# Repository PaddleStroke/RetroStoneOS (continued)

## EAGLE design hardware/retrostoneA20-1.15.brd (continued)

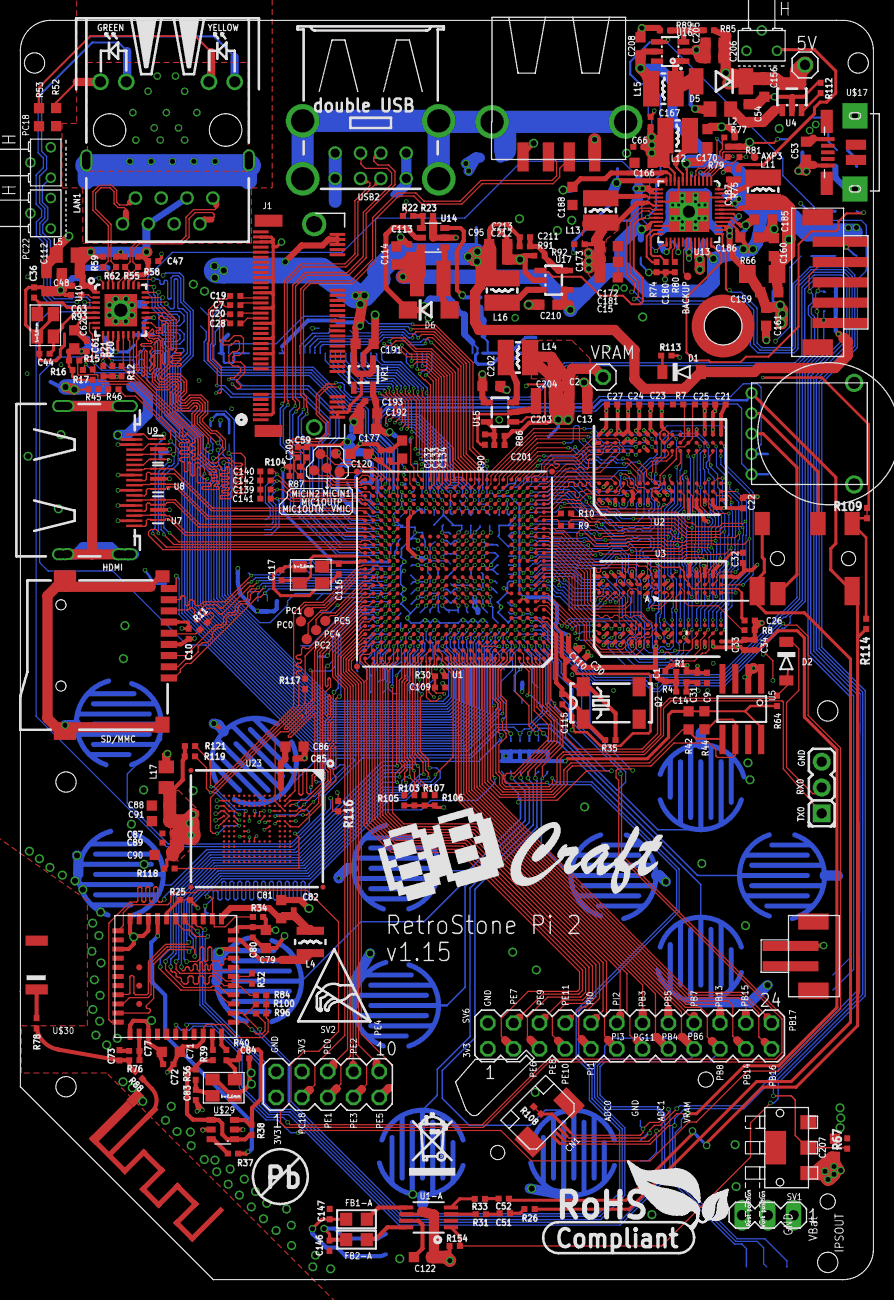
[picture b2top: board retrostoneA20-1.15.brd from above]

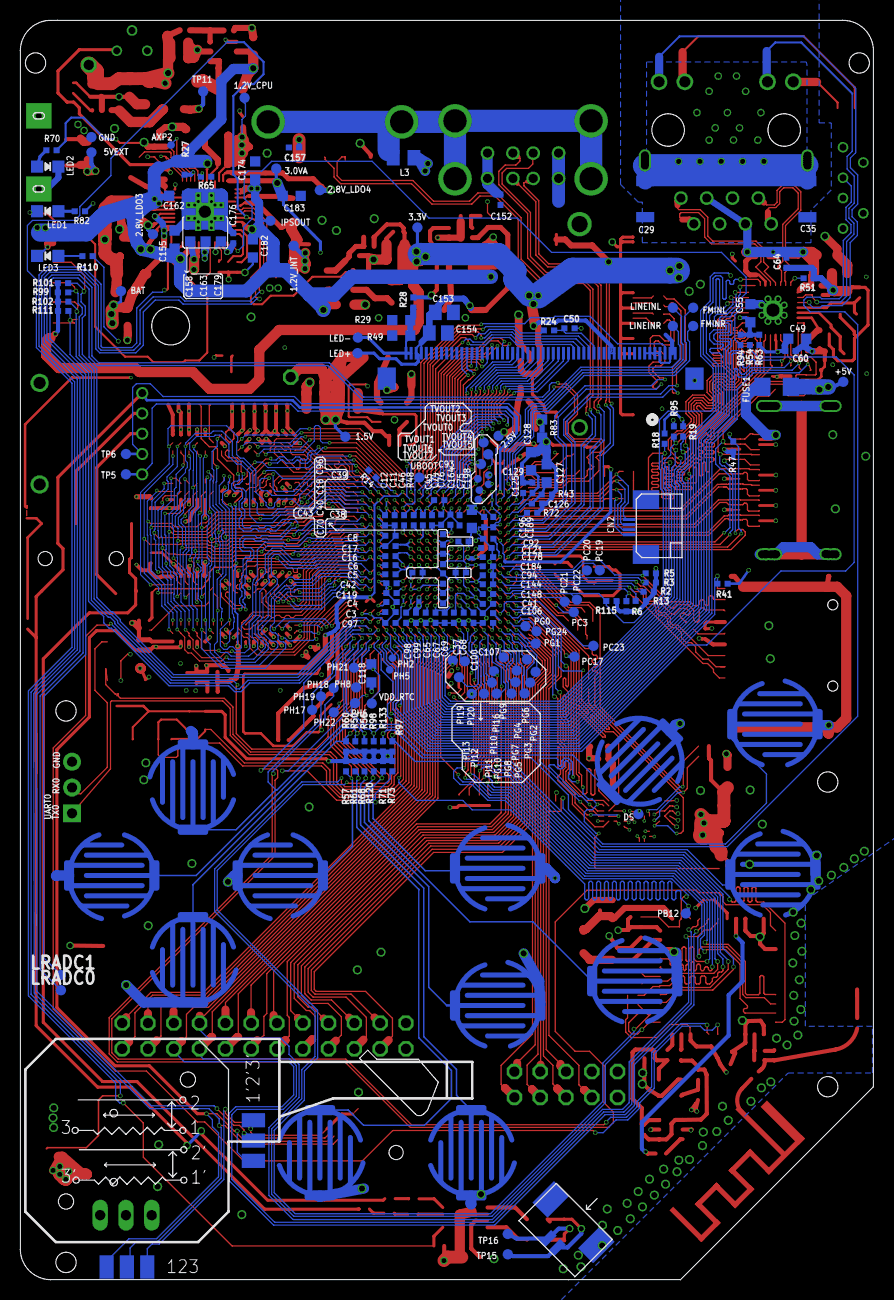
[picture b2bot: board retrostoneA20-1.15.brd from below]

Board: 4 copper layers, 84.0 x 124.0 mm, 477 parts (213 on the bottom side), 416 nets.

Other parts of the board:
U$9: PB
U$10: ESD_SYMBOL
U$11: RECYCLE_BIN1/8
U$12: ROHS
U$14: 8BCRAFTLOGO

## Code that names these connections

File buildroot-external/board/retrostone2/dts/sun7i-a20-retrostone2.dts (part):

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	/*
	 * Optional analog stick U$33 (FPC CN1, "Pro" part), read through the
	 * AXP209 ADC. The pots are fed from the 1.5 V net, the wipers go to AXP
	 * GPIO0 (X) and GPIO1 (Y). axp20x_adc raw unit is 0.5 mV, so full scale
	 * is ~3000. io-channels indexes are positions in axp20x_adc_channels[]:
	 * 5 = gpio0_v, 6 = gpio1_v (the old kernel exposed them as in_voltage3/4).
	 * X is inverted, like the production script (ABS_X = VREF - raw).
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	};

	/*
	 * PB2/PWM0 -> R22 -> CE of U14 (KA2707 LED boost), R23 pulls CE low.
	 * The boost runs from IPSOUT: there is no backlight enable GPIO and no
	 * backlight supply to switch (schematic v1.15).
	 */
	backlight: backlight {
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
	/*
	 * Face buttons, D-pad, START/SELECT. All switch to GND with an external
	 * 10k pull-up (active low). Every pin here is PH0-PH21, which have an
	 * external interrupt (EINTn) on the A20, so they are interrupt driven.
	 *
	 * Codes follow Documentation/input/gamepad.rst, which is positional:
	 * the Nintendo-style labels A (right) and B (bottom) map to BTN_EAST and
	 * BTN_SOUTH. This matches the production RetroArch autoconfig
	 * (PH0 = RetroPad A, PH11 = RetroPad B, PH12 = X, PH20 = Y).
	 * TODO(hw): confirm the physical A/B/X/Y positions on the case.
	 */
	gpio-keys {
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		button-a {
			label = "A";
			linux,code = <BTN_EAST>;
			gpios = <&pio 7 0 GPIO_ACTIVE_LOW>;	/* PH0, K2 */
		};

		button-b {
			label = "B";
			linux,code = <BTN_SOUTH>;
			gpios = <&pio 7 11 GPIO_ACTIVE_LOW>;	/* PH11, K4 */
		};

		button-x {
			label = "X";
			linux,code = <BTN_NORTH>;
			gpios = <&pio 7 12 GPIO_ACTIVE_LOW>;	/* PH12, K1 */
		};

		button-y {
			label = "Y";
			linux,code = <BTN_WEST>;
			gpios = <&pio 7 20 GPIO_ACTIVE_LOW>;	/* PH20, K3 */
		};

		/* Optional buttons (pads SELECT3/SELECT4 on the PCB) */
		button-c {
			label = "C";
			linux,code = <BTN_C>;
			gpios = <&pio 7 3 GPIO_ACTIVE_LOW>;	/* PH3, K5 */
		};

		button-z {
			label = "Z";
			linux,code = <BTN_Z>;
			gpios = <&pio 7 13 GPIO_ACTIVE_LOW>;	/* PH13, K6 */
		};

		button-start {
			label = "Start";
			linux,code = <BTN_START>;
			gpios = <&pio 7 14 GPIO_ACTIVE_LOW>;	/* PH14 */
		};

		button-select {
			label = "Select";
			linux,code = <BTN_SELECT>;
			gpios = <&pio 7 15 GPIO_ACTIVE_LOW>;	/* PH15 */
		};

		button-dpad-up {
			label = "D-pad Up";
			linux,code = <BTN_DPAD_UP>;
			gpios = <&pio 7 19 GPIO_ACTIVE_LOW>;	/* PH19 */
		};

		button-dpad-down {
			label = "D-pad Down";
			linux,code = <BTN_DPAD_DOWN>;
			gpios = <&pio 7 7 GPIO_ACTIVE_LOW>;	/* PH7 */
		};

		button-dpad-left {
			label = "D-pad Left";
			linux,code = <BTN_DPAD_LEFT>;
			gpios = <&pio 7 4 GPIO_ACTIVE_LOW>;	/* PH4 */
		};

		button-dpad-right {
			label = "D-pad Right";
			linux,code = <BTN_DPAD_RIGHT>;
			gpios = <&pio 7 16 GPIO_ACTIVE_LOW>;	/* PH16 */
		};
	};

	/*
	 * Shoulder buttons on the 5-pin JST connector U$4. PH22-PH27 have no
	 * EINT on the A20, so they are polled. Active low, external 10k pull-ups.
	 */
	gpio-keys-shoulder {
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		button-l1 {
			label = "L1";
			linux,code = <BTN_TL>;
			gpios = <&pio 7 23 GPIO_ACTIVE_LOW>;	/* PH23 */
		};

		button-r1 {
			label = "R1";
			linux,code = <BTN_TR>;
			gpios = <&pio 7 22 GPIO_ACTIVE_LOW>;	/* PH22 */
		};

		button-l2 {
			label = "L2";
			linux,code = <BTN_TL2>;
			gpios = <&pio 7 27 GPIO_ACTIVE_LOW>;	/* PH27 */
		};

		button-r2 {
			label = "R2";
			linux,code = <BTN_TR2>;
			gpios = <&pio 7 26 GPIO_ACTIVE_LOW>;	/* PH26 */
		};
	};

	/*
	 * Tact switches U$32 (PC18) and U$31 (PC22), active low with external
	 * 10k pull-ups. Port C has no EINT, so they are polled. The production
	 * firmware used them as brightness +/-; volume is an analog wheel, so
	 * brightness codes are the right default. Kept in their own input
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		key-brightness-up {
			label = "Brightness Up";
			linux,code = <KEY_BRIGHTNESSUP>;
			gpios = <&pio 2 18 GPIO_ACTIVE_LOW>;	/* PC18, U$32 */
		};

		key-brightness-down {
			label = "Brightness Down";
			linux,code = <KEY_BRIGHTNESSDOWN>;
			gpios = <&pio 2 22 GPIO_ACTIVE_LOW>;	/* PC22, U$31 */
		};
	};

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	leds {
		compatible = "gpio-leds";

		/* PH2 -> R110 (10k) -> LED3 (blue) -> GND: active high */
		led-0 {
			function = LED_FUNCTION_STATUS;
			color = <LED_COLOR_ID_BLUE>;
			gpios = <&pio 7 2 GPIO_ACTIVE_HIGH>;	/* PH2 */
			default-state = "off";
		};
	};
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	/* eMMC U23 reset (RST_N, 10k pull-up R121). Enabled by the emmc overlay. */
	mmc2_pwrseq: pwrseq-emmc {
		compatible = "mmc-pwrseq-emmc";
		reset-gpios = <&pio 2 16 GPIO_ACTIVE_LOW>;	/* PC16 */
		status = "disabled";
	};

	/* AP6210 WL_REG_ON and the 32.768 kHz LPO from CLK_OUT_A (PI12) */
	mmc3_pwrseq: pwrseq-wifi {
		compatible = "mmc-pwrseq-simple";
		reset-gpios = <&pio 7 9 GPIO_ACTIVE_LOW>;	/* PH9 WL_REG_ON */
		clocks = <&ccu CLK_OUT_A>;
		clock-names = "ext_clock";
		/* out-a resets to the 24 MHz parent: force 32.768 kHz from osc32k */
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
	/*
	 * 3.5" 640x480 parallel RGB panel on the FPC U$7. All 24 data lines
	 * (PD0-PD23), CLK (PD24 via R24), DE (PD25), HSYNC (PD26) and VSYNC
	 * (PD27) are wired, so the bus is RGB888 (the old U-Boot "depth:18" was
	 * wrong). The panel's SPI and reset pins are not connected to the SoC.
	 *
	 * Timings are the ones the production kernel patched into panel-simple:
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	/*
	 * USB port power: all three ports get +5V_USB from U4 (SY6280) whose EN
	 * is tied to +5V, so VBUS is always on and there is no VBUS GPIO.
	 * Do NOT use sunxi-common-regulators.dtsi: its PH6/PH3/PB8/PB9 GPIOs are
	 * the ethernet PHY reset option, button K5 and BT PCM lines here.
	 */
};
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 * LAN8710A (U10), MII. Straps: PHYAD0 (RXER) pulled up by R12, PHYAD1
 * (RXCLK) and PHYAD2 (RXD3) pulled down by R15/R16, so the address is 1.
 * RMIISEL (RXD2) pulled down by R17: MII. The PHY NRST is on the system
 * reset; the PH6 option (R54) is not fitted.
 */
&gmac {
	pinctrl-names = "default";
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	status = "okay";
};

/* Battery on U$18 with its NTC on the AXP TS pin */
&battery_power_supply {
	monitored-battery = <&battery>;	/* V_OFF and charge current, see &battery */
	status = "okay";
};

/* Analog stick wipers: put AXP GPIO0/GPIO1 in ADC mode (pinctrl hog) */
&axp_gpio {
	pinctrl-names = "default";
	pinctrl-0 = <&axp_gpio0_adc_pin>, <&axp_gpio1_adc_pin>;

	axp_gpio0_adc_pin: gpio0-adc-pin {
		pins = "GPIO0";
		function = "adc";
	};

	axp_gpio1_adc_pin: gpio1-adc-pin {
		pins = "GPIO1";
		function = "adc";
	};
};
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};

/*
 * AT24C16 EEPROM U5 on TWI1 (PB18/PB19). Disabled: on the first hardware
 * boot (2026-09-26) the bus was stuck ("i2c i2c-1: mv64xxx: I2C bus locked",
 * twice, 2 s each), which cost 4.2 s of boot time, and nothing uses the EEPROM.
 * TODO(hw): check whether U5 and the pull-ups R42/R44 are fitted.
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};

/*
 * microSD, card detect PH1 with the external 47k pull-up R41.
 * post-power-on-delay-ms: the MMC core waits this long twice while "powering
 * up" the card before its first command (default 10 ms each, on the path to
 * the root filesystem). The card supply is the always-on 3.3 V rail, powered
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&mmc0 {
	vmmc-supply = <&reg_vcc3v3>;
	bus-width = <4>;
	cd-gpios = <&pio 7 1 GPIO_ACTIVE_LOW>;	/* PH1 */
	post-power-on-delay-ms = <1>;
	status = "okay";
};

/*
 * eMMC U23 (KLMAG2GEND, 16 GB, "Pro" part). Its DAT4-DAT7 are wired to
 * PC12-PC15, but the A20 has no SDC2 function on those pins (the 6.18
 * pinctrl driver only offers it on the R40), so the bus is 4-bit.
 * Enabled by the emmc overlay.
 */
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		reg = <1>;
		compatible = "brcm,bcm4329-fmac";
		interrupt-parent = <&pio>;
		interrupts = <7 10 IRQ_TYPE_LEVEL_LOW>;	/* PH10 / EINT10 WL_HOST_WAKE */
		interrupt-names = "host-wake";
	};
};
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};

&pio {
	/* 32.768 kHz LPO for the AP6210 WiFi and BT (PI12 = CLK_OUT_A) */
	pinctrl-names = "default";
	pinctrl-0 = <&clk_out_a_pin>;

	lcd0_rgb888_pins: lcd0-rgb888-pins {
		pins = "PD0", "PD1", "PD2", "PD3", "PD4", "PD5",
		       "PD6", "PD7", "PD8", "PD9", "PD10", "PD11",
		       "PD12", "PD13", "PD14", "PD15", "PD16", "PD17",
		       "PD18", "PD19", "PD20", "PD21", "PD22", "PD23",
		       "PD24", "PD25", "PD26", "PD27";
		function = "lcd0";
	};
};
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	};
};

/* Debug console, header "UART0" (PB22 TX, PB23 RX) */
&uart0 {
	pinctrl-names = "default";
	pinctrl-0 = <&uart0_pb_pins>;
	status = "okay";
};

/* AP6210 Bluetooth: UART2 on PI16-PI19 with RTS/CTS */
&uart2 {
	pinctrl-names = "default";
	pinctrl-0 = <&uart2_pi_pins>, <&uart2_cts_rts_pi_pins>;
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	 * AP6210 BT (BCM20710), modelled like sun7i-a20-cubietruck.dts; the
	 * RetrOrangePi image loaded ap6210/bcm20710a1.hcd and BT worked.
	 * Units with an AP6212 would need "brcm,bcm43430a1-bt" instead.
	 * PH25 has no EINT, so host wake cannot be an interrupt (as on the
	 * Cubietruck).
	 */
	bluetooth {
		compatible = "brcm,bcm20702a1";
		clocks = <&ccu CLK_OUT_A>;
		clock-names = "lpo";
		device-wakeup-gpios = <&pio 7 24 GPIO_ACTIVE_LOW>;	/* PH24 BT_WAKE */
		host-wakeup-gpios = <&pio 7 25 GPIO_ACTIVE_LOW>;	/* PH25 BT_HOST_WAKE */
		shutdown-gpios = <&pio 7 18 GPIO_ACTIVE_HIGH>;	/* PH18 BT_RST_N */
		max-speed = <1500000>;
	};
};
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
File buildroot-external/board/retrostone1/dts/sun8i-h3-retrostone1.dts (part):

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	};

	/*
	 * Optional analog stick on JOYSTICK_CON (4 pins: 3.3 V, VRY, GND, VRX),
	 * read by the MCP3208 ADC (U$35) on SPI1: CH0 = Y, CH1 = X. 12-bit,
	 * VREF = 3.3 V. The io-channels index is the MCP3208 single-ended
	 * channel number. With no stick fitted the inputs float.
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		button-a {
			label = "A";
			linux,code = <BTN_EAST>;
			gpios = <&pio 3 14 GPIO_ACTIVE_LOW>;	/* PD14, K2 */
		};

		button-b {
			label = "B";
			linux,code = <BTN_SOUTH>;
			gpios = <&pio 3 15 GPIO_ACTIVE_LOW>;	/* PD15, K4 */
		};

		button-x {
			label = "X";
			linux,code = <BTN_NORTH>;
			gpios = <&pio 3 13 GPIO_ACTIVE_LOW>;	/* PD13, K1 */
		};

		button-y {
			label = "Y";
			linux,code = <BTN_WEST>;
			gpios = <&pio 3 9 GPIO_ACTIVE_LOW>;	/* PD9, K3 */
		};

		/*
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		button-c {
			label = "C";
			linux,code = <BTN_C>;
			gpios = <&pio 4 3 GPIO_ACTIVE_LOW>;	/* PE3, SELECT3 */
		};

		button-z {
			label = "Z";
			linux,code = <BTN_Z>;
			gpios = <&pio 2 9 GPIO_ACTIVE_LOW>;	/* PC9, SELECT4 */
		};

		button-start {
			label = "Start";
			linux,code = <BTN_START>;
			gpios = <&pio 3 1 GPIO_ACTIVE_LOW>;	/* PD1 */
		};

		button-select {
			label = "Select";
			linux,code = <BTN_SELECT>;
			gpios = <&pio 3 4 GPIO_ACTIVE_LOW>;	/* PD4 */
		};

		button-dpad-up {
			label = "D-pad Up";
			linux,code = <BTN_DPAD_UP>;
			gpios = <&pio 3 12 GPIO_ACTIVE_LOW>;	/* PD12, AU */
		};

		button-dpad-down {
			label = "D-pad Down";
			linux,code = <BTN_DPAD_DOWN>;
			gpios = <&pio 3 5 GPIO_ACTIVE_LOW>;	/* PD5, AD */
		};

		button-dpad-left {
			label = "D-pad Left";
			linux,code = <BTN_DPAD_LEFT>;
			gpios = <&pio 3 0 GPIO_ACTIVE_LOW>;	/* PD0, AL */
		};

		button-dpad-right {
			label = "D-pad Right";
			linux,code = <BTN_DPAD_RIGHT>;
			gpios = <&pio 3 11 GPIO_ACTIVE_LOW>;	/* PD11, AR */
		};

		/* Shoulder buttons: the 5-pin JST connector U$4 */
		button-l1 {
			label = "L1";
			linux,code = <BTN_TL>;
			gpios = <&pio 3 8 GPIO_ACTIVE_LOW>;	/* PD8, U$4 pin 1 */
		};

		button-r1 {
			label = "R1";
			linux,code = <BTN_TR>;
			gpios = <&pio 3 3 GPIO_ACTIVE_LOW>;	/* PD3, U$4 pin 2 */
		};

		button-l2 {
			label = "L2";
			linux,code = <BTN_TL2>;
			gpios = <&pio 3 6 GPIO_ACTIVE_LOW>;	/* PD6, U$4 pin 4 */
		};

		button-r2 {
			label = "R2";
			linux,code = <BTN_TR2>;
			gpios = <&pio 3 7 GPIO_ACTIVE_LOW>;	/* PD7, U$4 pin 3 */
		};
	};

	/*
	 * Side tact switch U$15 on PA1 (external 10k pull-up R113), the only
	 * side button wired to the SoC (U$36-U$38 are the AMT630A's own keys,
	 * on its ADC input). It is the power key: a short press is a clean
	 * power-off (the frontend's power module, board.ini power_key_device =
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		key-power {
			label = "Power";
			linux,code = <KEY_POWER>;
			gpios = <&pio 0 1 GPIO_ACTIVE_LOW>;	/* PA1, U$15 */
			debounce-interval = <20>;
		};
	};
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};

/*
 * microSD, card detect PF6 with the external 10k pull-up R16. The card is
 * on the always-on 3.3 V rail: no ramp to wait for (see the RetroStone2
 * DTS).
 */
&mmc0 {
	vmmc-supply = <&reg_vcc3v3>;
	bus-width = <4>;
	cd-gpios = <&pio 5 6 GPIO_ACTIVE_LOW>;	/* PF6 */
	post-power-on-delay-ms = <1>;
	status = "okay";
};

/*
 * No eMMC and no on-board WiFi: PG0-PG5 (SDIO), PL0 (WIFI_EN), PL7
 * (WIFI-POWER-EN) and PA11 (WL-WAKE-HOST) only go to test pads JP8-JP16 for
 * an optional module, which is not described here.
 */

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};

/*
 * MCP3208 8-channel 12-bit ADC U$35 on SPI1 (PA13 CS, PA14 CLK, PA15 MOSI,
 * PA16 MISO): CH0/CH1 = the analog stick. CH2 is wired straight to VBAT
 * with no divider, so with VREF = 3.3 V it saturates for any charged cell:
 * no battery level (docs/boards.md). CH3-CH7 go to test pads.
 */
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	status = "okay";
};

/* Debug console, header UART0-DBG (PA4 TX, PA5 RX through D1), 115200 */
&uart0 {
	pinctrl-names = "default";
	pinctrl-0 = <&uart0_pa_pins>;
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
